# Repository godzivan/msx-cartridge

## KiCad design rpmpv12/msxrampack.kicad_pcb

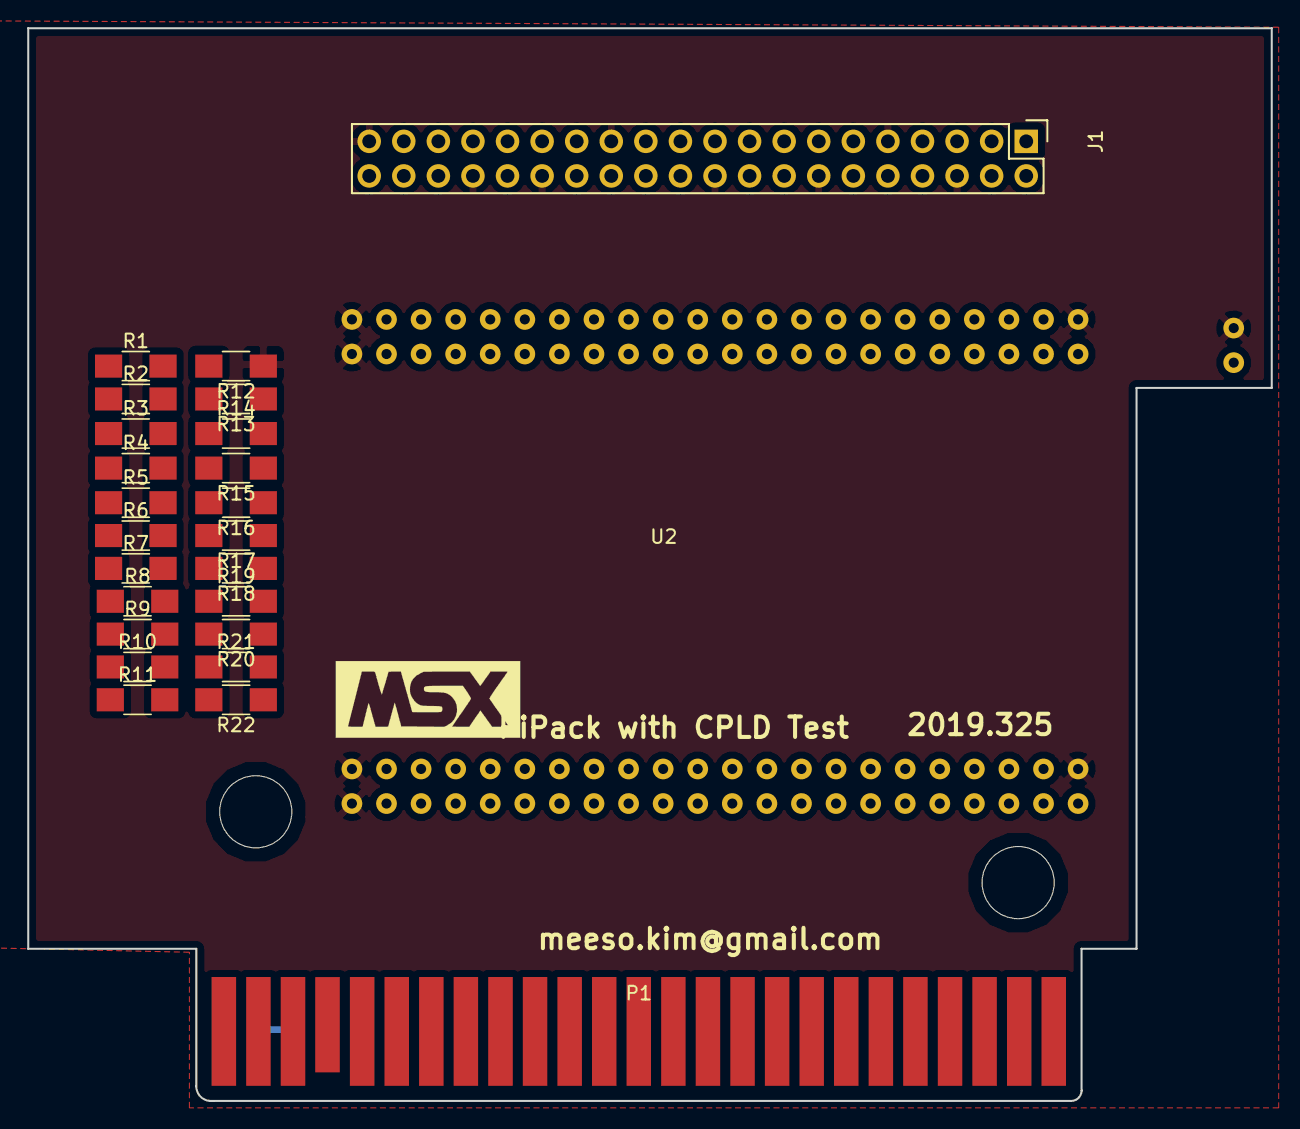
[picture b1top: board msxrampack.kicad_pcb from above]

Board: 2 copper layers, 91.3 x 78.8 mm, 25 parts (0 on the bottom side), 89 nets.

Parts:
J1: RPi_GPIO; Pin_Header_Straight_2x20
P1: MSX_SLOT; card_edge_connector
R1, R2, R3, R4, R5, R6, R7, R8, R9, R10, R11: 1K; R_1206_HandSoldering
R12, R13, R14, R15, R16, R17, R18, R19, R20, R21, R22: 0.5K; R_1206_HandSoldering
U2: CPLD; emp270_board

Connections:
+5V: J1.2, J1.4, P1.45, P1.47, U2.89
/3V3: J1.1, J1.17, U2.3, U2.43, U2.46
/A0: P1.28, U2.18
/A1: P1.27, U2.19
/A2: P1.30, U2.16
/A3: P1.29, U2.17
/A4: P1.32, U2.14
/A5: P1.31, U2.15
/A6: P1.22, U2.24
/A7: P1.21, U2.25
/A8: P1.24, U2.22
/A9: P1.17, U2.29
/A10: P1.20, U2.26
/A11: P1.19, U2.27
/A12: P1.23, U2.23
/A13: P1.26, U2.20
/A14: P1.25, U2.21
/A15: P1.18, U2.28
/BUSDIR: P1.10, U2.35
/CLOCK: P1.42, U2.5
/D0: P1.34, U2.12
/D1: P1.33, U2.13
/D2: P1.36, U2.10
/D3: P1.35, U2.11
/D4: P1.38, U2.8
/D5: P1.37, U2.9
/D6: P1.40, U2.6
/D7: P1.39, U2.7
/INT: P1.8, U2.37
/IORQ: P1.11, U2.34
/M1: P1.9, U2.36
/MERQ: P1.12, U2.33
/RA8: J1.24, U2.62
/RA9: J1.21, U2.59
/RA10: J1.19, U2.58
/RA11: J1.23, U2.61
/RA12: J1.32, U2.68
/RA13: J1.33, U2.69
/RA14: J1.8, U2.49
/RA15: J1.10, U2.51
/RA18: J1.12, U2.53
/RC16: J1.36, U2.71
/RC17: J1.11, U2.52
/RC19: J1.35, U2.70
/RC20: J1.38, U2.73
/RC21: J1.40, U2.74
/RC22: J1.15, U2.55
/RC23: J1.16, U2.56
/RC24: J1.18, U2.57
/RC25: J1.22, U2.60
/RC26: J1.37, U2.72
/RC27: J1.13, U2.54
/RD: P1.14, U2.31
/RD0: J1.28, U2.65
/RD1: J1.27, U2.64
/RD2: J1.3, U2.47
/RD3: J1.5, U2.48
/RD4: J1.7, U2.50
/RD5: J1.29, U2.66
/RD6: J1.31, U2.67
/RD7: J1.26, U2.63
/RESET: P1.15, U2.4, U2.30
/RFSH: P1.6, U2.39
/SLTSL: P1.4, U2.40
/SND1: R2.2, U2.85
/SND2: R3.2, U2.84
/SND3: R4.2, U2.83
/SND4: R5.2, U2.82
/SND5: R6.2, U2.81
/SND6: R7.2, U2.80
/SND7: R8.2, U2.79
/SND8: R9.2, U2.78
/SND9: R10.2, U2.77
/SND10: R11.2, U2.76
/SOUNDIN: P1.49, R11.1, R22.2
/SW: P1.44, P1.46
/WAIT: P1.7, U2.38
/WR: P1.13, U2.32
GND: J1.6, J1.9, J1.14, J1.20, J1.25, J1.30, J1.34, J1.39, P1.41, P1.43, R12.1, U2.1, U2.2, U2.44, U2.45, U2.87, U2.88, U2.90
unnamed: R1.1, R12.2, R13.1
unnamed: R10.1, R21.2, R22.1
unnamed: R2.1, R13.2, R14.1
unnamed: R3.1, R14.2, R15.1
unnamed: R4.1, R15.2, R16.1
unnamed: R5.1, R16.2, R17.1
unnamed: R6.1, R17.2, R18.1
unnamed: R7.1, R18.2, R19.1
unnamed: R8.1, R19.2, R20.1
unnamed: R9.1, R20.2, R21.1

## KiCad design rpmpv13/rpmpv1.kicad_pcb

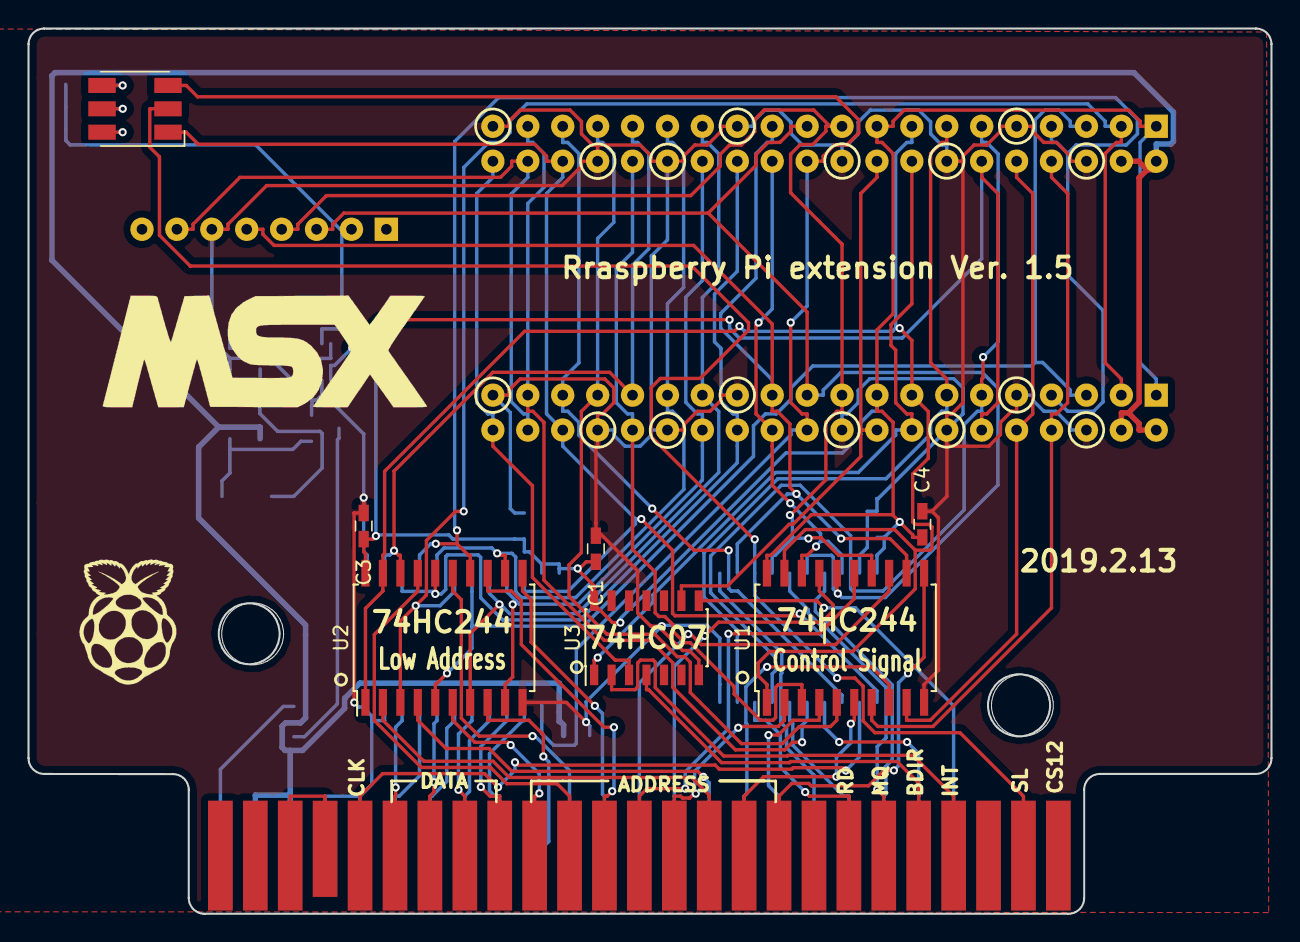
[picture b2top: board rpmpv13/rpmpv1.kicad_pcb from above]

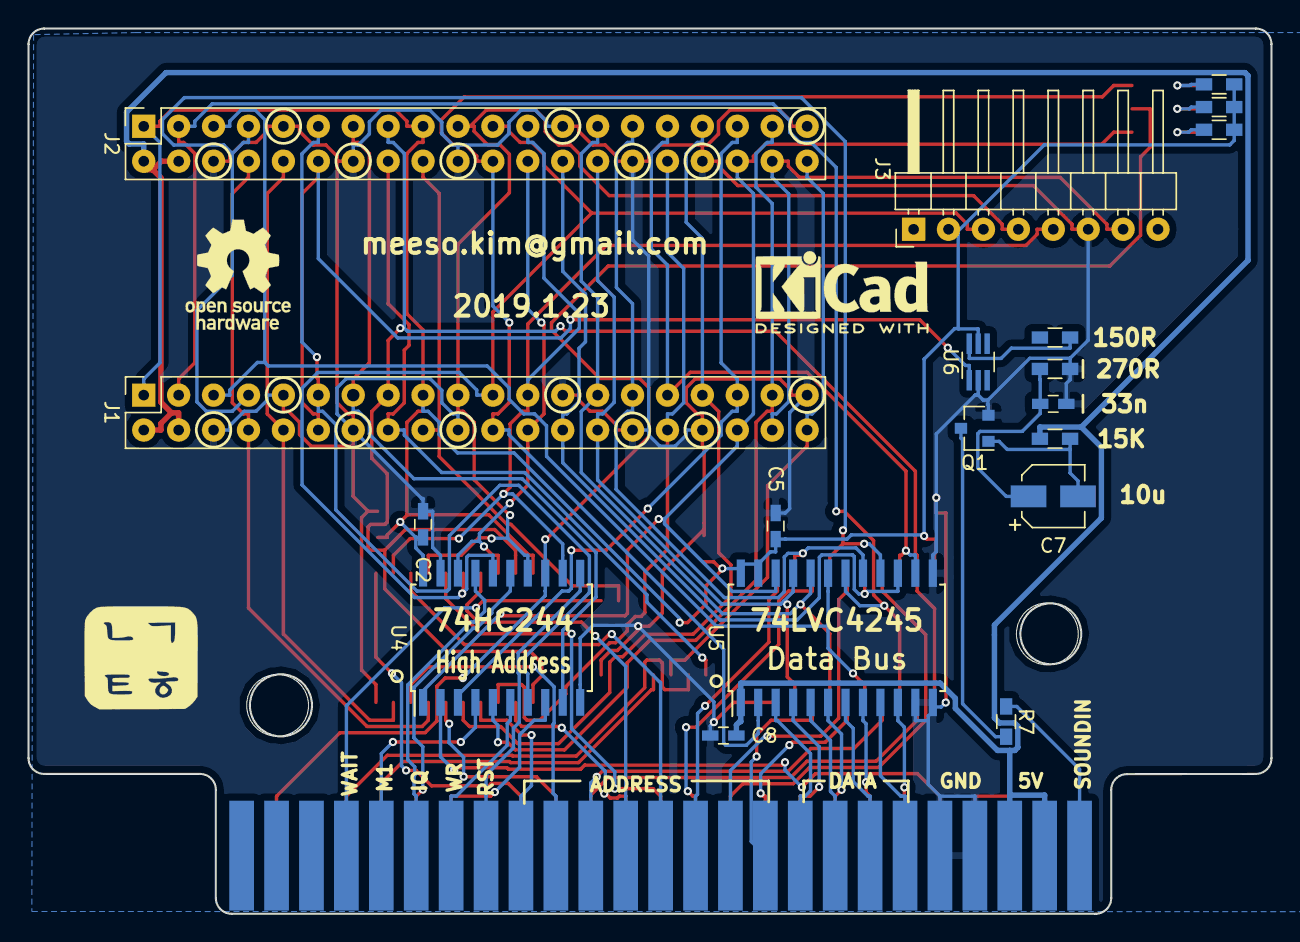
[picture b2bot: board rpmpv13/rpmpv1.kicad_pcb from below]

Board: 2 copper layers, 90.4 x 64.4 mm, 31 parts (21 on the bottom side), 75 nets.

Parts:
C1, C2, C3, C4, C5, C6, C8: C; C_0603_HandSoldering
C7: CP; CP_Elec_4x4.5
D1: LED_RGB; LED_RGB_5050-6
G1: LOGO; raspberry_pi_logo
G2: LOGO; msx-logo
J1, J2: RPi_GPIO; Socket_Strip_Straight_2x20_Pitch2.54mm
J3: Conn_01x08; Pin_Header_Angled_1x08_Pitch2.54mm
P1: CONN_02X25; card_edge_connector
Q1: Q_NPN_BEC; SOT-23
R1, R2, R3, R4, R5, R6, R7: R; R_0603_HandSoldering
REF2: OSHW-Logo_7.5x8mm_SilkScreen
REF3: KiCad-Logo2_6mm_SilkScreen
U1, U2, U4: 74HC244; SOIC-20W_7.5x12.8mm_Pitch1.27mm
U3: 74LS07; SOIC-14_3.9x8.7mm_Pitch1.27mm
U5: LVC4245; SOIC-24W_7.5x15.4mm_Pitch1.27mm
U6: NC7WZ16; SOT-363_SC-70-6_Handsoldering

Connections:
+3V3: C1.1, C2.1, C3.1, C4.1, C5.1, J1.1, J1.17, J2.1, J2.17, J3.2, R1.2, R2.2, R3.2, U1.20, U2.20, U3.14, U4.20, U5.23, U5.24, U6.5
+5V: C8.2, J1.2, J1.4, J2.2, J2.4, P1.45, P1.47, R6.1, U5.1
/A0: P1.28, U2.13
/A1: P1.27, U2.11
/A2: P1.30, U2.17
/A3: P1.29, U2.15
/A4: P1.32, U2.6
/A5: P1.31, U2.8
/A6: P1.22, U2.2
/A7: P1.21, U2.4
/A8: P1.24, U1.2
/A9: P1.17, U1.4
/A10: P1.20, U1.6
/A11: P1.19, U1.8
/A12: P1.23, U1.17
/A13: P1.26, U1.15
/A14: P1.25, U1.13
/A15: P1.18, U1.11
/ADDR: J1.15, J2.15, U1.1, U1.19, U2.1, U2.19
/BUSDIR: P1.10, U3.4
/CE0: J1.38, J2.38, J3.7
/CLK: P1.42, U4.2
/D0: P1.34, U5.4
/D1: P1.33, U5.3
/D2: P1.36, U5.6
/D3: P1.35, U5.5
/D4: P1.38, U5.8
/D5: P1.37, U5.7
/D6: P1.40, U5.10
/D7: P1.39, U5.9
/DAT_DIR: D1.3, J1.22, J2.22, U5.2
/DAT_EN: D1.1, J1.36, J2.36, U4.1, U5.22
/INT: P1.8, U3.2
/IORQ: P1.11, U4.17
/M1: P1.9, U4.4
/MISO: J1.21, J2.21, J3.3, U1.16, U4.16
/MOSI: J1.19, J2.19, J3.4, U1.14, U4.14
/MREQ: P1.12, U4.15
/RA8: J1.24, J2.24, U1.18, U4.18
/RA11: J1.23, J2.23, J3.5, U1.12, U4.12
/RA12: J1.32, J2.32, U1.3
/RA13: J1.33, J2.33, U1.5
/RA14: J1.8, J2.8, U1.7
/RA15: J1.10, J2.10, U1.9
/RC17: J1.11, J2.11, U4.7
/RC18: J1.12, J2.12, U6.1
/RC19: J1.35, J2.35, U4.3
/RC21: J1.40, J2.40, U3.3
/RC23: J1.16, J2.16, U3.1
/RC24: J1.18, J2.18, U3.9
/RC26: J1.37, J2.37, U4.5
/RC27: J1.13, J2.13, U4.9
/RD: P1.14, U4.8
/RD0: J1.27, J2.27, U2.7, U5.20
/RD1: J1.28, J2.28, U2.9, U5.21
/RD2: J1.3, J2.3, U2.3, U5.18
/RD3: J1.5, J2.5, U2.5, U5.19
/RD4: J1.7, J2.7, U2.14, U5.16
/RD5: J1.29, J2.29, U2.12, U5.17
/RD6: J1.31, J2.31, U2.18, U5.14
/RD7: J1.26, J2.26, U2.16, U5.15
/RESET: P1.15, U4.11
/SLTSL: D1.2, P1.4, U4.13
/SOUNDIN: P1.49, R7.1
/WAIT: P1.7, U3.8
/WR: P1.13, U4.6
GND: C1.2, C2.2, C3.2, C4.2, C5.2, C6.2, C8.1, J1.6, J1.9, J1.14, J1.20, J1.25, J1.30, J1.34, J1.39, J2.6, J2.9, J2.14, J2.20, J2.25, J2.30, J2.34, J2.39, J3.6, P1.41, P1.43, Q1.2, R5.2, U1.10, U2.10, U3.7, U4.10, U4.19, U5.11, U5.12, U5.13, U6.2
unnamed: C6.1, C7.1, R5.1
unnamed: C7.2, Q1.1, R6.2
unnamed: D1.4, R3.1
unnamed: D1.5, R2.1
unnamed: D1.6, R1.1
unnamed: P1.44, P1.46
unnamed: Q1.3, R7.2
unnamed: R4.1, U6.6

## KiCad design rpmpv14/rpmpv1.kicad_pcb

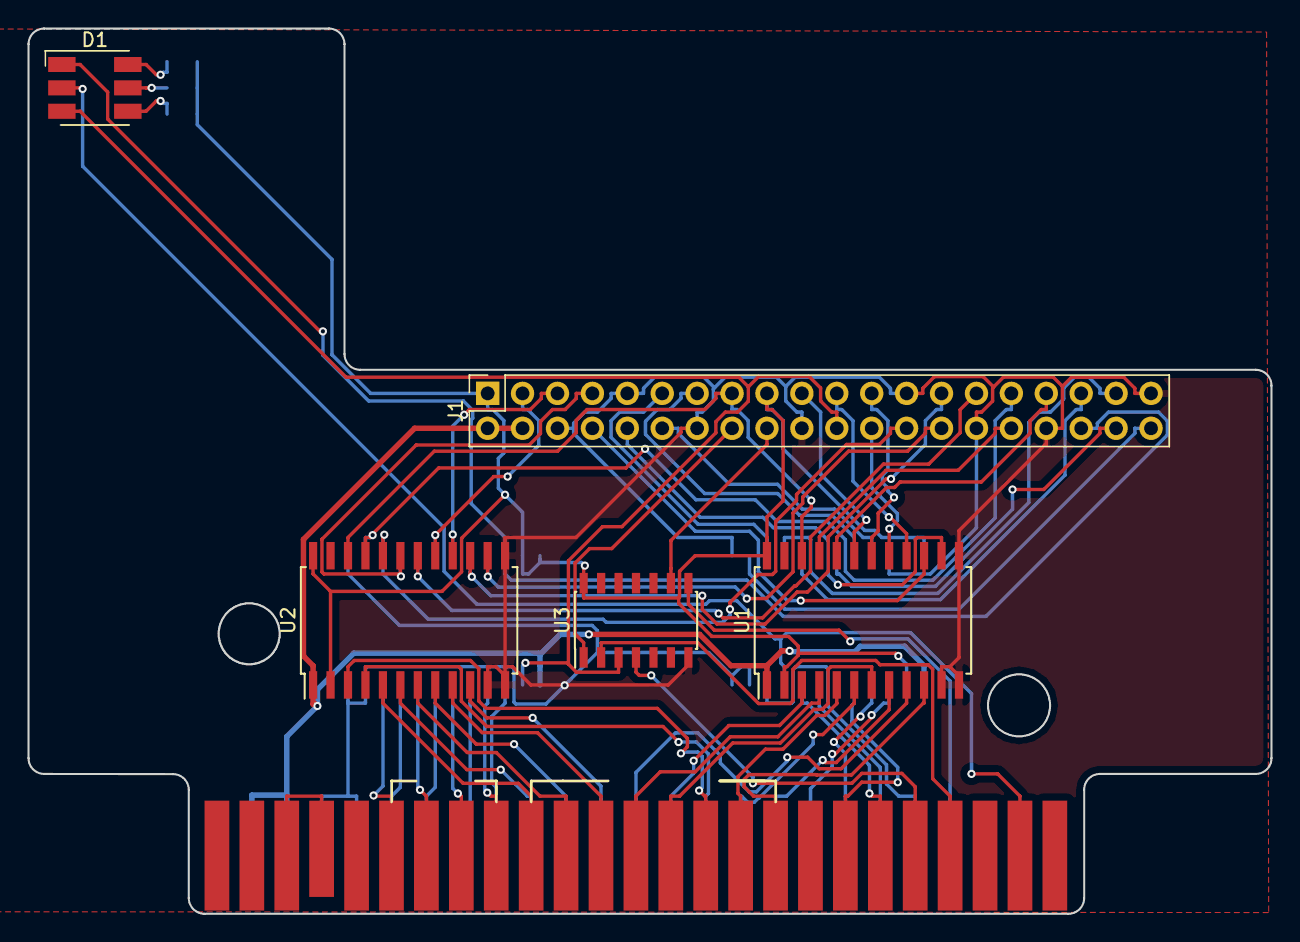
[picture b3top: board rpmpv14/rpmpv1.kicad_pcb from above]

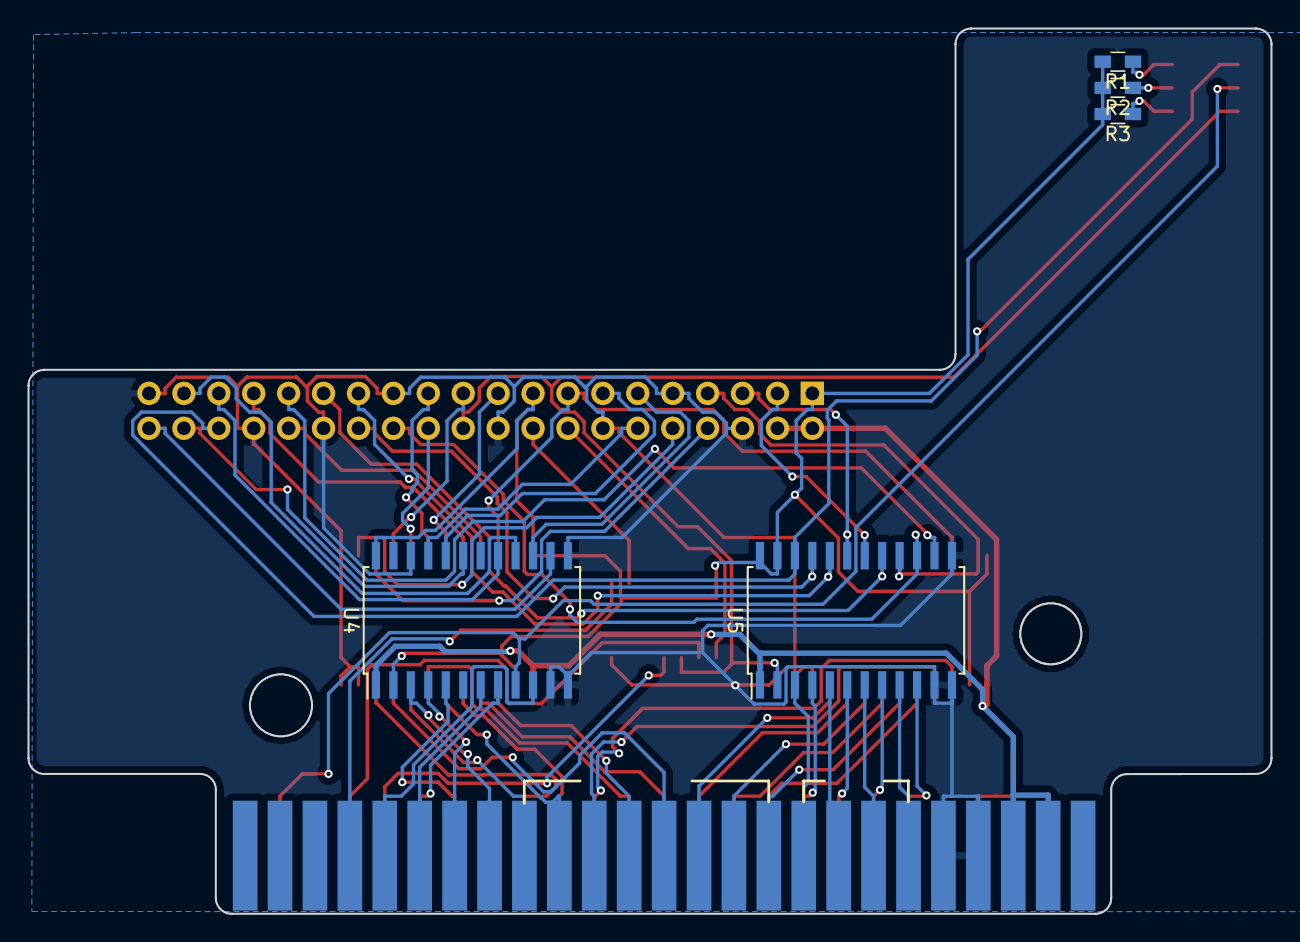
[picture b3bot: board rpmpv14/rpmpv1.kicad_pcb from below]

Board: 2 copper layers, 90.4 x 64.4 mm, 11 parts (5 on the bottom side), 69 nets.

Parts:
D1: LED_RGB; LED_RGB_5050-6
J1: RPi_GPIO; Socket_Strip_Straight_2x20_Pitch2.54mm
P1: CONN_02X25; card_edge_connector
R1, R2, R3: R; R_0603_HandSoldering
U1, U2, U4, U5: LVC4245; SOIC-24W_7.5x15.4mm_Pitch1.27mm
U3: 74LS07; SOIC-14_3.9x8.7mm_Pitch1.27mm

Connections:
+3V3: J1.1, J1.17, R1.2, R2.2, R3.2, U1.2, U1.24, U2.2, U2.24, U3.14, U4.2, U4.24, U5.23, U5.24
+5V: J1.2, J1.4, P1.45, P1.47, U1.1, U2.1, U4.1, U5.1
/A0: P1.28, U2.9
/A1: P1.27, U2.10
/A2: P1.30, U2.7
/A3: P1.29, U2.8
/A4: P1.32, U2.5
/A5: P1.31, U2.6
/A6: P1.22, U2.3
/A7: P1.21, U2.4
/A8: P1.24, U1.7
/A9: P1.17, U1.8
/A10: P1.20, U1.5
/A11: P1.19, U1.6
/A12: P1.23, U1.3
/A13: P1.26, U1.4
/A14: P1.25, U1.9
/A15: P1.18, U1.10
/ADDR: J1.15, U1.22, U2.22
/BUSDIR: P1.10, U3.4
/D0: P1.34, U5.4
/D1: P1.33, U5.3
/D2: P1.36, U5.6
/D3: P1.35, U5.5
/D4: P1.38, U5.8
/D5: P1.37, U5.7
/D6: P1.40, U5.10
/D7: P1.39, U5.9
/DAT_DIR: D1.3, J1.22, U3.3, U5.2
/DAT_EN: D1.1, J1.36, U5.22
/INT: P1.8, U3.2
/IORQ: P1.11, U4.7
/M1: P1.9, U4.10
/MREQ: P1.12, U4.8
/RA8: J1.24, U1.17
/RA9: J1.21, U1.16
/RA10: J1.19, U1.19
/RA11: J1.23, U1.18
/RA12: J1.32, U1.21
/RA13: J1.33, U1.20
/RA14: J1.8, U1.15
/RA15: J1.10, U1.14
/RC17: J1.11, U4.15
/RC18: J1.12, U4.21
/RC19: J1.35, U4.17
/RC20: J1.38, U4.19
/RC21: J1.40, U4.14
/RC23: J1.16, U3.1
/RC24: J1.18, U3.9
/RC26: J1.37, U4.16
/RC27: J1.13, U4.20
/RD: P1.14, U4.5
/RD0: J1.27, U2.15, U5.20
/RD1: J1.28, U2.14, U5.21
/RD2: J1.3, U2.17, U5.18
/RD3: J1.5, U2.16, U5.19
/RD4: J1.7, U2.19, U5.16
/RD5: J1.29, U2.18, U5.17
/RD6: J1.31, U2.21, U5.14
/RD7: J1.26, U2.20, U5.15
/RESET: P1.15, U4.3
/SLTSL: D1.2, P1.4, U4.9
/WAIT: P1.7, U3.8
/WR: P1.13, U4.4
GND: J1.6, J1.9, J1.14, J1.20, J1.25, J1.30, J1.34, J1.39, P1.41, P1.43, U1.11, U1.12, U1.13, U2.11, U2.12, U2.13, U3.7, U4.11, U4.12, U4.13, U4.22, U5.11, U5.12, U5.13
unnamed: D1.4, R3.1
unnamed: D1.5, R2.1
unnamed: D1.6, R1.1
unnamed: P1.44, P1.46

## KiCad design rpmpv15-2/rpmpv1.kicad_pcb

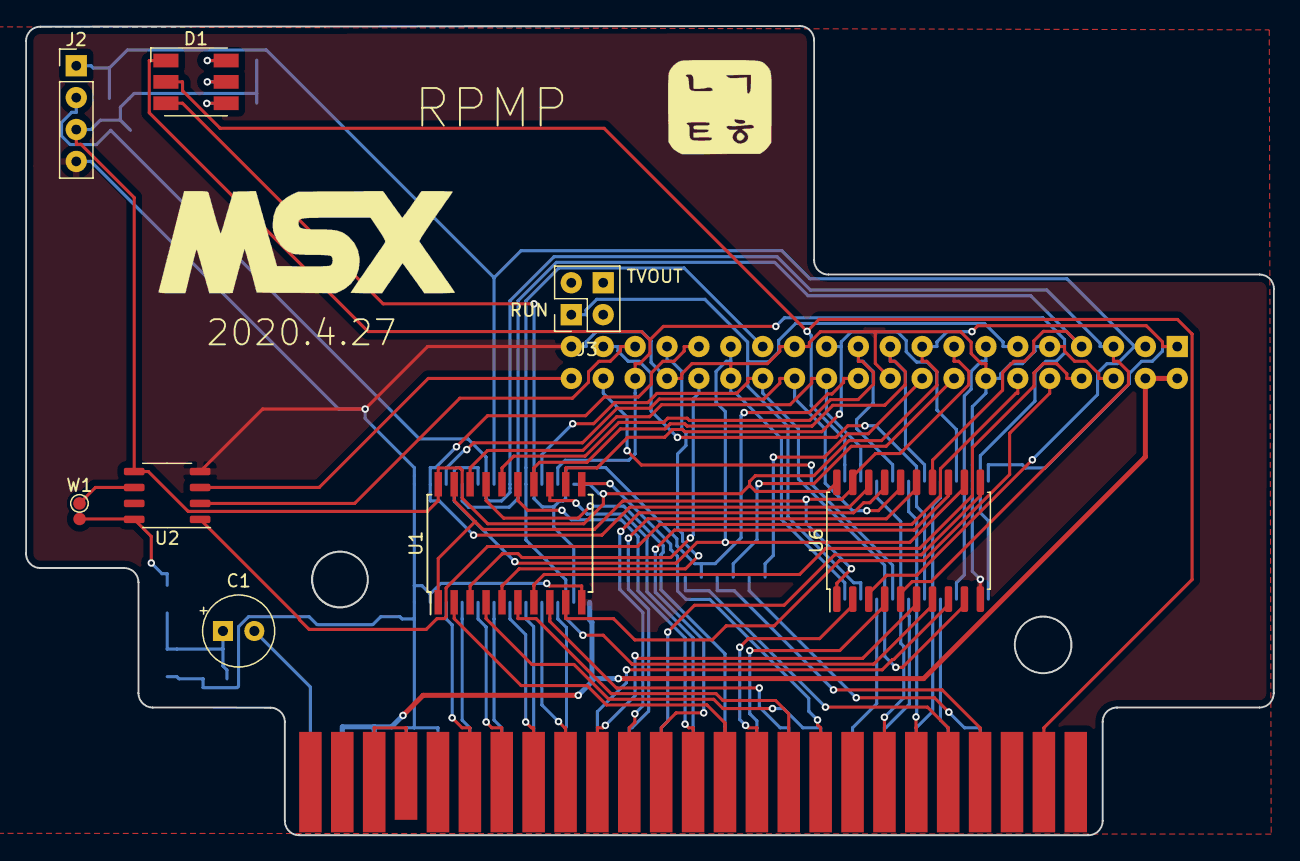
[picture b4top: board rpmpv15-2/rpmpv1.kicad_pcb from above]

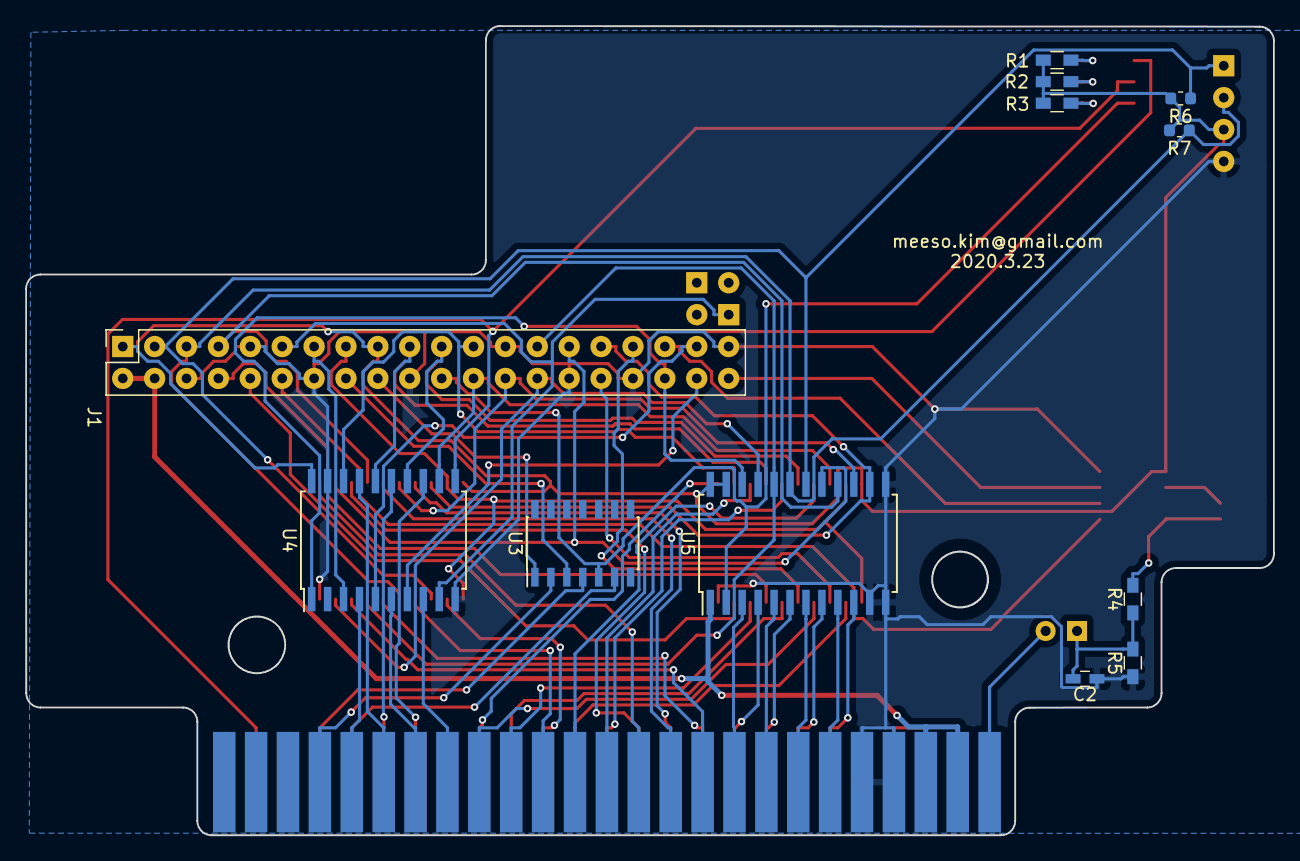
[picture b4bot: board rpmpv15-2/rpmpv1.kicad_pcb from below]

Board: 2 copper layers, 99.4 x 64.5 mm, 23 parts (12 on the bottom side), 73 nets.

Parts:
C1: CP; CP_Radial_Tantal_D5.5mm_P2.50mm
C2: C; C_0603_HandSoldering
D1: LED_RGB; LED_RGB_5050-6
G1: LOGO; msx-logo
G2: LOGO; srxg
J1: RPi_GPIO; PinSocket_2x20_P2.54mm_Vertical
J2: Conn_01x04; Pin_Header_Straight_1x04_Pitch2.54mm
J3: Conn_02x02_Counter_Clockwise; PinSocket_2x02_P2.54mm_Vertical
P1: CONN_02X25; card_edge_connector
R1, R2, R3, R4, R5: R; R_0603_HandSoldering
R6, R7: R; R_0603_1608Metric
U1, U4: 74HC244; SOIC-20W_7.5x12.8mm_Pitch1.27mm
U2: PT8211; SOP-8_3.9x4.9mm_P1.27mm
U3: 74LS07; SOIC-14_3.9x8.7mm_Pitch1.27mm
U5: LVC4245; SOIC-24W_7.5x15.4mm_Pitch1.27mm
U6: 74HC244; SOIC-20W_7.5x12.8mm_P1.27mm
W1: TEST_1P; TestPoint_Pad_D1.0mm

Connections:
+3V3: J1.1, J1.17, J2.3, R1.2, R2.2, R3.2, R6.2, R7.2, U1.20, U2.5, U4.20, U5.23, U5.24, U6.20
+5V: J1.2, J1.4, P1.45, P1.47, U5.1
/A0: P1.28, U6.13
/A1: P1.27, U6.11
/A2: P1.30, U6.17
/A3: P1.29, U6.15
/A4: P1.32, U6.6
/A5: P1.31, U6.8
/A6: P1.22, U6.2
/A7: P1.21, U6.4
/A8: P1.24, U1.2
/A9: P1.17, U1.4
/A10: P1.20, U1.6
/A11: P1.19, U1.8
/A12: P1.23, U1.17
/A13: P1.26, U1.15
/A14: P1.25, U1.13
/A15: P1.18, U1.11
/ADDR: J1.15, U1.1, U1.19, U6.1, U6.19
/BUSDIR: P1.10, U3.6
/D0: P1.34, U5.4
/D1: P1.33, U5.3
/D2: P1.36, U5.6
/D3: P1.35, U5.5
/D4: P1.38, U5.8
/D5: P1.37, U5.7
/D6: P1.40, U5.10
/D7: P1.39, U5.9
/DAT_DIR: D1.3, J1.22, U3.5, U5.2
/DAT_EN: D1.1, J1.36, U4.1, U5.22
/INT: P1.8, U3.4
/IORQ: P1.11, U4.17
/M1: P1.9, U4.4
/MREQ: P1.12, U4.15
/RA8: J1.24, U1.18, U4.12
/RA9: J1.21, U1.16, U4.14
/RA10: J1.19, U1.14, U4.16
/RA11: J1.23, U1.12, U4.18
/RA12: J1.32, U1.3
/RA13: J1.33, U1.5
/RA14: J1.8, U1.7
/RA15: J1.10, U1.9
/RC17: J1.11, J3.1, U4.9
/RC18: J1.12, U2.1
/RC19: J1.35, U2.2
/RC20: J1.38, U4.7
/RC21: J1.40, U2.3
/RC23: J1.16, U3.3
/RC24: J1.18, U3.1
/RC26: J1.37, U4.5
/RC27: J1.13, U4.3
/RD: P1.14, U4.13
/RD0: J1.27, U5.20, U6.7
/RD1: J1.28, U5.21, U6.9
/RD2: J1.3, J2.1, R6.1, U5.18, U6.3
/RD3: J1.5, J2.2, R7.1, U5.19, U6.5
/RD4: J1.7, U5.16, U6.14
/RD5: J1.29, U5.17, U6.12
/RD6: J1.31, U5.14, U6.18
/RD7: J1.26, U5.15, U6.16
/RESET: P1.15, U4.8
/SLTSL: D1.2, P1.4, U4.11
/SND: R4.2, U2.8, W1.2
/SOUNDIN: C1.2, P1.49
/WAIT: P1.7, U3.2
/WR: P1.13, U4.6
GND: C2.1, J1.6, J1.9, J1.14, J1.20, J1.25, J1.30, J1.34, J1.39, J2.4, P1.41, P1.43, R5.1, U1.10, U2.4, U4.10, U4.19, U5.11, U5.12, U5.13, U6.10
unnamed: C1.1, C2.2, R4.1, R5.2
unnamed: D1.4, R3.1
unnamed: D1.5, R2.1
unnamed: D1.6, R1.1
unnamed: P1.44, P1.46
unnamed: U2.6, W1.1

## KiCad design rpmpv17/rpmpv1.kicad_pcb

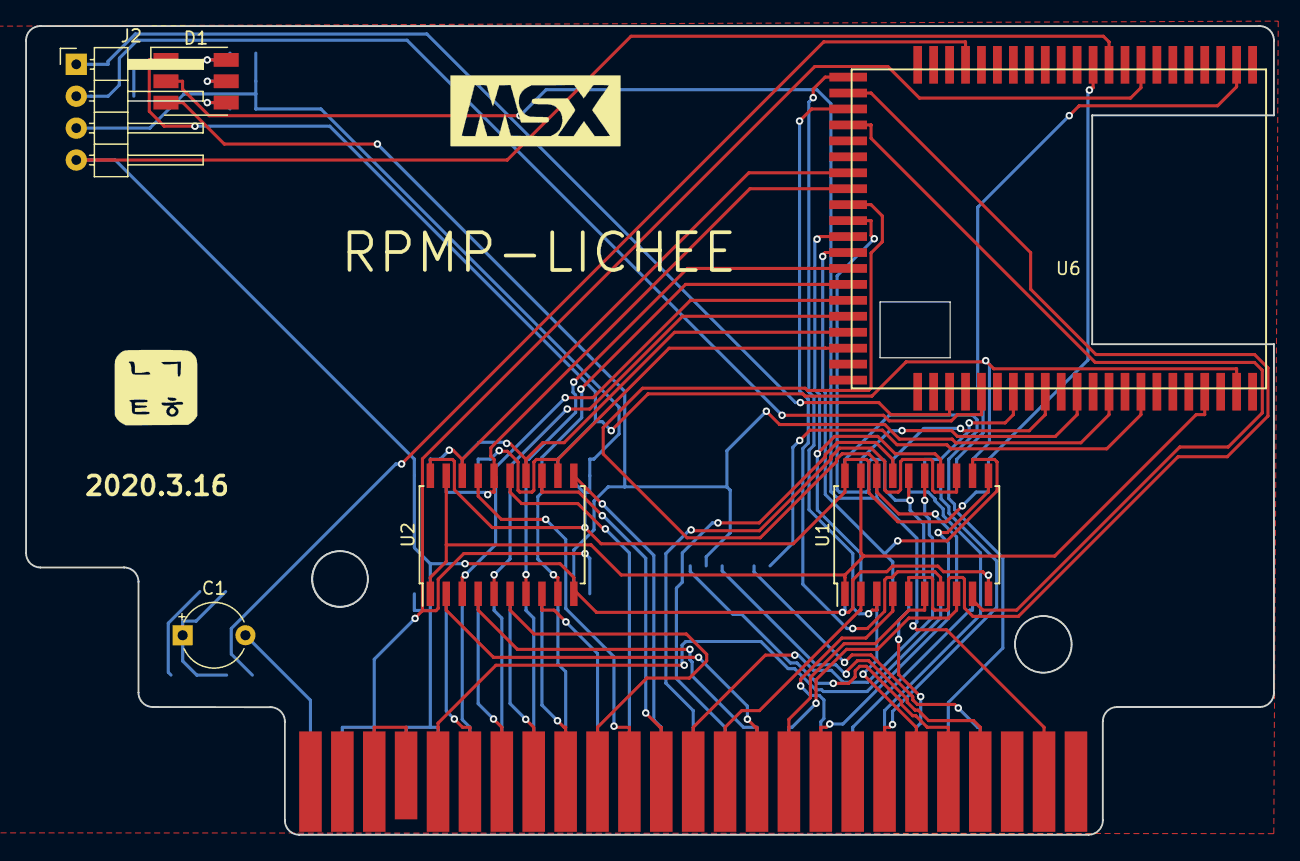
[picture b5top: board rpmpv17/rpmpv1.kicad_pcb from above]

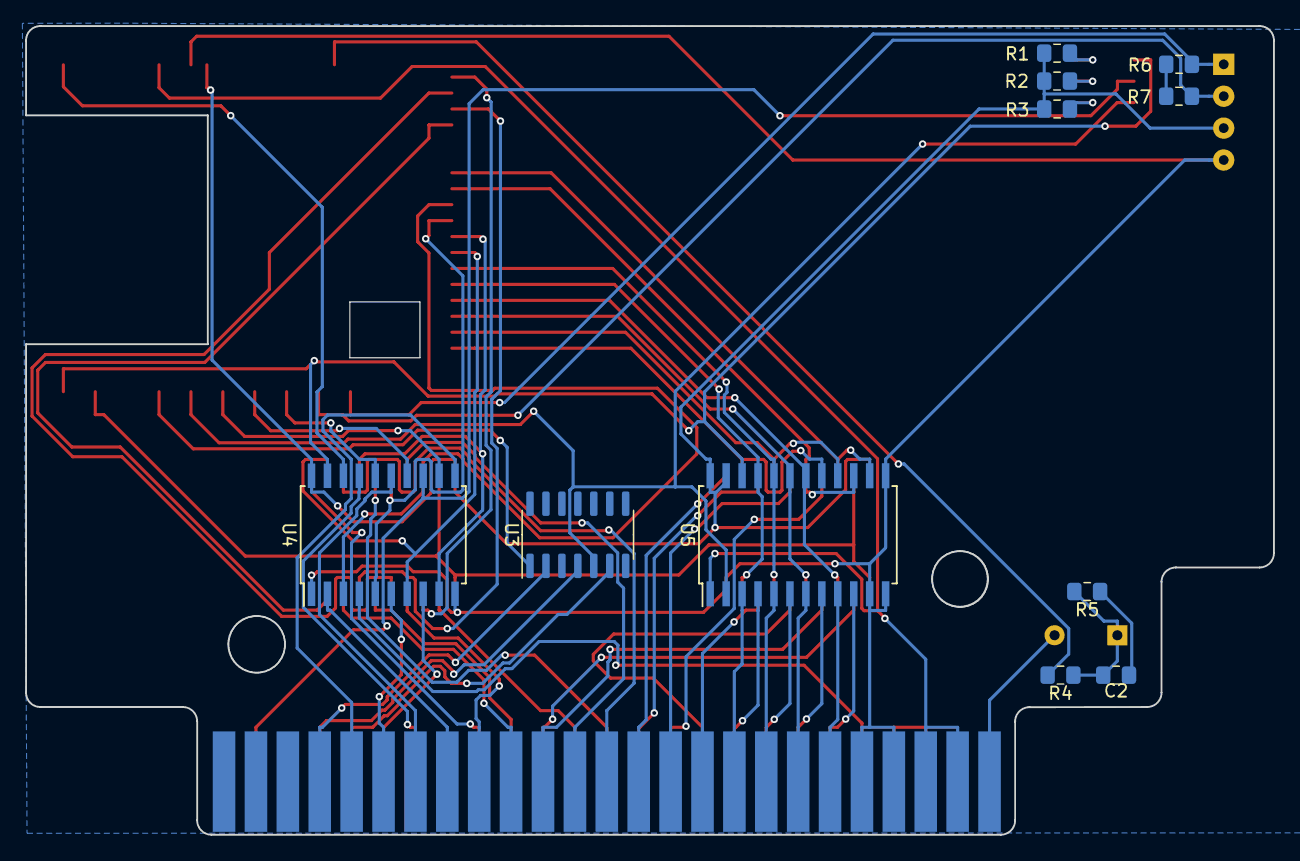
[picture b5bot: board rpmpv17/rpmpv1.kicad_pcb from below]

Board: 2 copper layers, 99.4 x 64.4 mm, 20 parts (11 on the bottom side), 73 nets.

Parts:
C1: CP; CP_Radial_Tantal_D5.0mm_P5.00mm
C2: C; C_0805_2012Metric_Pad1.15x1.40mm_HandSolder
D1: LED_RGB; LED_RGB_5050-6
G1: LOGO; srxg10
G2: LOGO
J2: Conn_01x04; PinHeader_1x04_P2.54mm_Horizontal
P1: CONN_02X25; card_edge_connector
R1, R2, R3, R4, R5, R6, R7: R; R_0805_2012Metric_Pad1.15x1.40mm_HandSolder
U1, U2, U4: 74HC244; SOIC-20W_7.5x12.8mm_Pitch1.27mm
U3: 74LS07; SOIC-14_3.9x8.7mm_P1.27mm
U5: LVC4245; SOIC-24W_7.5x15.4mm_Pitch1.27mm
U6: licheepi_nano

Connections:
/3V3: R6.1, R7.1
/5V0: P1.45, P1.47, U5.1, U6.8
/A0: P1.28, U2.13
/A1: P1.27, U2.11
/A2: P1.30, U2.17
/A3: P1.29, U2.15
/A4: P1.32, U2.6
/A5: P1.31, U2.8
/A6: P1.22, U2.2
/A7: P1.21, U2.4
/A8: P1.24, U1.2
/A9: P1.17, U1.4
/A10: P1.20, U1.6
/A11: P1.19, U1.8
/A12: P1.23, U1.17
/A13: P1.26, U1.15
/A14: P1.25, U1.13
/A15: P1.18, U1.11
/ADDR: U1.1, U1.19, U2.1, U2.19, U6.61
/BUSDIR: P1.10, U3.6
/CLK: P1.42, U4.4
/D0: P1.34, U5.4
/D1: P1.33, U5.3
/D2: P1.36, U5.6
/D3: P1.35, U5.5
/D4: P1.38, U5.8
/D5: P1.37, U5.7
/D6: P1.40, U5.10
/D7: P1.39, U5.9
/DAT_DIR: D1.3, U3.5, U5.2, U6.55
/DAT_EN: D1.1, U4.19, U5.22, U6.63
/GND: J2.4, P1.41, P1.43, U1.10, U2.10, U4.1, U4.10, U5.11, U5.12, U5.13, U6.10
/INT: P1.8, U3.4
/IORQ: P1.11, U4.6
/M1: P1.9, U4.11
/MREQ: P1.12, U4.8
/RA8: U1.18, U4.3, U6.31
/RA9: U1.16, U4.5, U6.32
/RA10: U1.14, U4.9, U6.33
/RA11: U1.12, U4.7, U6.34
/RA12: U1.3, U6.23
/RA13: U1.5, U6.24
/RA14: U1.7, U6.25
/RA15: U1.9, U6.26
/RC18: R4.2, U6.19
/RCLK: U4.16, U6.49
/RD: P1.14, U4.17
/RD0: U2.7, U5.20, U6.35
/RD1: U2.9, U5.21, U6.36
/RD2: U2.3, U5.18, U6.37
/RD3: U2.5, U5.19, U6.38
/RD4: U2.14, U5.16, U6.39
/RD5: U2.12, U5.17, U6.40
/RD6: U2.18, U5.14, U6.29
/RD7: U2.16, U5.15, U6.30
/RESET: P1.15, U4.2
/RIORQ: U4.14, U6.51
/RMREQ: U4.12, U6.53
/RRST: U4.18, U6.2
/RWAIT: U3.1, U6.57
/SCK: J2.2, R7.2, U6.47
/SDA: J2.1, R6.2, U6.45
/SLTSL: D1.2, P1.4, U4.13
/SOUNDIN: C1.2, P1.49
/VCC: J2.3, R1.2, R2.2, R3.2, U1.20, U2.20, U4.20, U5.23, U5.24, U6.11
/WAIT: P1.7, U3.2
/WR: P1.13, U4.15
unnamed: C1.1, C2.2, R4.1, R5.2
unnamed: C2.1, R5.1
unnamed: D1.4, R3.1
unnamed: D1.5, R2.1
unnamed: D1.6, R1.1
unnamed: P1.44, P1.46
